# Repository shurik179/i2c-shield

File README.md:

# i2c-shield

 An I2C shield for Feather and ItsyBitsy boards, making it easy to connect I2C devices to boards without Stemma QT/Qwiic connectors without fiddling with breadboard.

It is similar to this product by Sparkfun: https://www.sparkfun.com/products/16790 but provides more features:

* can be used with Feather or ItsyBitsy boards

* provides two Qwiic/Stemma QT connectors, and a male 4-pin header

* provides pull-up resistors (3.3K) on SDA and SCL lines. They    can be disconnected by breaking the solder bridge next to them using a sharp knife or a similar tool.

*  provides  four test points (Keystone 5000 or compatible, e.g. https://www.adafruit.com/product/3824), for connecting oscilloscope probes - very handy when you need to debug I2C connection.

The board is designed in KiCad 6.0  RC1.

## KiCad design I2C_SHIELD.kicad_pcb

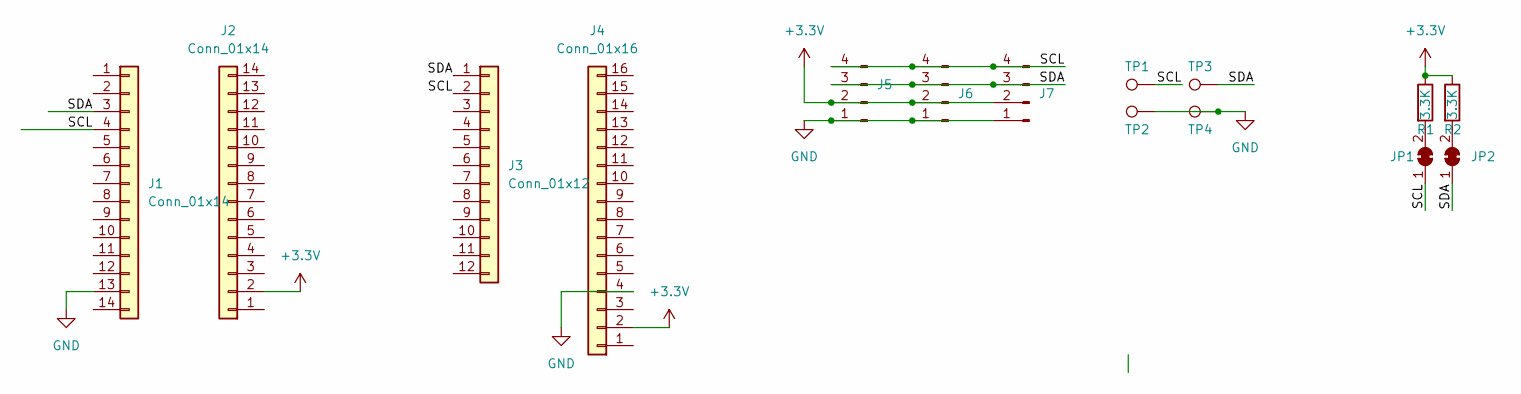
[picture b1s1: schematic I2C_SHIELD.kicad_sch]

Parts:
J1, J2: Conn_01x14; PinSocket_1x14_P2.54mm_Vertical
J3: Conn_01x12; PinSocket_1x12_P2.54mm_Vertical
J4: Conn_01x16; PinSocket_1x16_P2.54mm_Vertical
J5, J6: Conn_01x04_Male; JST_SH_SM04B-SRSS-TB_1x04-1MP_P1.00mm_Horizontal
J7: Conn_01x04_Male; PinHeader_1x04_P2.54mm_Vertical
JP1, JP2: SolderJumper_2_Bridged; SolderJumper-2_P1.3mm_Bridged
R1, R2: 3.3K; R_0805_2012Metric
TP1, TP2, TP3, TP4: TestPoint; TestPoint_Keystone_5000-5004_Miniature

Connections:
+3V3: J2.2, J4.2, J5.2, J6.2, J7.2, R1.1, R2.1
/SCL: J1.4, J3.2, J5.4, J6.4, J7.4, JP1.1 (A), TP1.1
/SDA: J1.3, J3.1, J5.3, J6.3, J7.3, JP2.1 (A), TP3.1
GND: J1.13, J4.4, J5.1, J6.1, J7.1, TP2.1, TP4.1
unnamed: JP1.2 (B), R1.2
unnamed: JP2.2 (B), R2.2

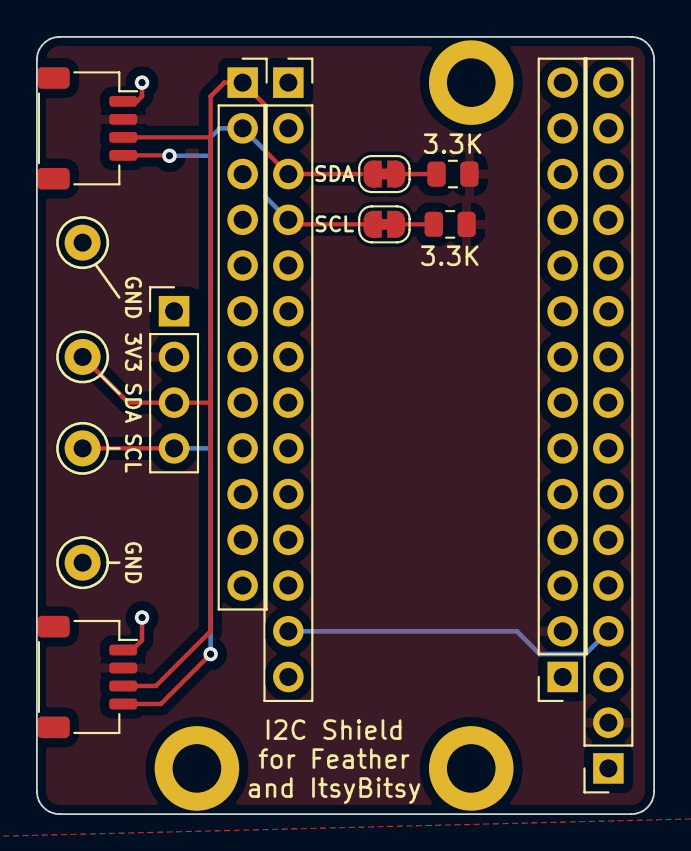
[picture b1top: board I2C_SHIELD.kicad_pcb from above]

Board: 2 copper layers, 34.3 x 43.2 mm, 15 parts (0 on the bottom side), 6 nets.

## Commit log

2021-12-08 Initial upload
2021-12-08 updated screenshot
2021-12-08 updating .gitignore
